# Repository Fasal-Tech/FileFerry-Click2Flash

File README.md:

# 🚀 FileFerry-Click2Flash

A compact and portable tool designed for easy factory programming of your IoT product. 🌐 Transfer files, binary images, security credentials, or certificates from an SD card or from a Serial terminal over USB to a target SPI flash IC with just a click of a button. 🎯

This repository contains all the necessary files to manufacture your own samples from JLCPCB (or a vendor of your choice) and start using it right away

The included firmware source code and compiled binaries can be used right out of the box! 🛠️ You can also modify the design and code and build your own custom product. ✨

## Product Image

The "FileFerry-Click2Flash" PCB.

The "FileFerry-Click2Flash" PCB with the pogo pins.

## 📁 Repository Contents

* **/Hardware 🛠️**
  * All Eagle design files (.brd, .sch)
* **/Firmware 💻**
  * Pre-compiled binaries to flash the board
  * Firmware source code (STM32Cube IDE, HAL) that you can use to modify the functionality
* **/Manufacturing 🏭**
  * All manufacturing files, including Gerber, BOM, PnP_XY, and prototype manufacturing files (Order BOM and PnP) that can be used to order directly from JLCPCB for a complete PCBA job.
* **/Assets 📸**
  * GitHub assets like images and other resources
* **/Demo 📸**
  * Demonstration resources to compile the firmware, flash it to the "FileFerry-Click2Flash" board and use it.

## 🔍 What is FileFerry-Click2Flash?

In its simplest form, FileFerry-Click2Flash is a low-cost, portable hardware jig that allows you to flash any external SPI flash IC (like the W25Q64JVSSIQ). 🛠️

You can transfer data in one of two ways:

1. Store your file/data in the onboard micro SD card. 💾
    1. Example: Production firmware images, common security tokens, certificates, etc.
2. Transfer the files from an external computer over UART using the X-modem protocol. 🔄
    1. Example: Device-specific unique keys, device-specific CA certificates, UUID tokens, etc.

You can do all of this with just a click of the onboard button! 🎯

## 🚀 Why is "FileFerry-Click2Flash" Needed? 🛠️

In today's fast-paced manufacturing environment, the need for efficient, reliable, and cost-effective tools is paramount. Traditional methods of programming SPI flash ICs, such as using J-link SPI programmers or bed-of-nails jigs, often involve expensive, bulky, and complex setups that are not easily adaptable to different production scenarios. 😓

This is where FileFerry-Click2Flash comes in! 🎉 It addresses the gap between high-cost, inflexible tools and the need for a versatile, portable, and user-friendly solution. Whether you are flashing firmware or transferring security credentials, or unique device identifiers, FileFerry-Click2Flash offers an ultra-low-cost alternative that is not only easy to use but also highly customizable. The ability to transfer files via an onboard SD card or over UART using the X-modem protocol provides flexibility in various production environments, making it a robust and indispensable tool for manufacturers, developers, and technicians alike. ⚙️💻

With its customizable connector interface and portable design, this tool simplifies the flashing process, reducing both the time and costs associated with traditional methods. FileFerry-Click2Flash is the modern solution to the challenges faced in programming SPI flash ICs, ensuring that the process is as seamless and efficient as possible. 🖊️💡

## 💰 Manufacturing Cost Breakdown

We got 5 quantity PCBA samples from JLCPCB. (We are in no way affiliated with JLCPCB—it's just convenient to manufacture quick prototypes with them!) 🚀

* Total cost with Shipping (PCB + PCBA): $132.49 📦
* Landing cost with import duties, customs, etc.: INR 14,000.00 (for 5 pieces) 💸
* Cost per board: INR 2,800.00 (includes 6 extra pogo pins, hand soldered later) 🛠️
* At a cost of INR 2,800.00 (~ USD 33.00), we have a SPI flasher with additional functionalities like UART transfer.
  
🔄 Compare this with a J-Flash SPI programmer at ~ USD 330.00 or a Bed of nails test jig at ~ USD 500.00.
🤔 Which would you choose?

## High Level Working

Let's look at how this works.

The "FileFerry-Click2Flash" system block diagram.

The "FileFerry-Click2Flash" PCB points

### There are two ways (currently supported) to transfer files to the target SPI Flash

### 1. Using the onboard micro SD card (Files need to be on the SD card)

  1. Simple copy the file you want to transfer to the external SPI Flash into the SD card (Example a production binary)
  2. Modify the given source code to use the file name and build the code
  3. Flash the code to the "FileFerry-Click2Flash" board
  4. Insert the SD Card, power up the board and click the "Flash" button for the flashing to take place
  5. you can monitor the progress on the RGB LED as well as debug logs on the USB-UART

### 2. Using a PC client over USB (you will need a Software client to initiate transfer)

  1. No re-programming needed.
  2. Slide the "Mode Switch" S302 to "Mode 1". This will activate UART X-Modem transfer. (Current firmware supports X-modem. Can be modified to any thing else).
  3. Open a terminal program of your choice. The terminal program has to support "File Transfer" functionality.
  4. We use TeraTerm. So open TeraTerm.
  5. Connect to the proper COM port. Use BAud as 115200,8N1.
  
  Teraterm Open

  6. Go to File-> Transfer -> XMODEM -> Send -> [Check Option 1K] + Select file.
  
  Transfer setting

  7. Select your file and click "Open".
  
  File Selection

  8. The file transfer will start.
  
  File Transfer

## What type of Files can I transfer?
The sky is the limit really. Some common examples are:

1. Transferring the production "Golden Image" of the product where the end product's bootloader performs a DFU from the binaries available in the Flash IC. (You can extend this for implementing OTA).
2. Transferring unique device CA certificates from a PC based on the device serial number. (Scan barcode, generate unique CA certificate in the PC application, transfer it to the device over USB UART).
3. Transferring audio files, JSON configuration files, etc.

## Can I modify the hardware?

You have the design files with you. You can do anything! If you are a student or a DIY'er, here are some ideas to use the hardware:

1. Use as a STM32F103 development kit
2. Use it as a data-logger. Examples:
   * Connect an I2C sensor (there is a QWIIC port for easy connection. There is also a JST port with controlled power) and modify the STM32 code to read from the sensor and store it in the onboard SD card.
   * You can connect a SPI sensor as well.
3. Use the additional UART2 port to connect a GPS receiver and modify the STM32 code to receive the GPS NMEA strings, parse it and store it in the onboard SD card.
4. RFID access control anyone? Interface a RFID reader over UART/I2C/SPI (RC522 or PN532 or similar), have a master list of RFID numbers stored in the SD card. Connect a relay to a free GPIO and give access control to the room.

Limitless possibilities!

## 📜 License Information
The hardware and firmware are released under the MIT License. 📝 The code is beerware; if you see me (or any other Fasal employee) at the local, and you've found our code helpful, please buy us a round! 🍻

Distributed as-is; no warranty is given. ⚠️ Read the License file for complete licensing information.

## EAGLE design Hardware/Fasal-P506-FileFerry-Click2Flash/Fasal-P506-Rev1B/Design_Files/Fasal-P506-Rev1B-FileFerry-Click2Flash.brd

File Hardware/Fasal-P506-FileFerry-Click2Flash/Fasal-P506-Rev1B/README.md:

# FileFerry-Click2Flash - Hardware Files #

This directory contains all the Hardware related files for the main "FileFerry-Click2Flash" Board.

# Repository Contents #
* **/Design_Files**
	* CubeMX Files
	* Change log
	* Design Report
	* Schematic pdf
	* Schematic Source (.sch)
	* Board Source (.brd)
* **/Manufacturing_Files**
	* PCBA BOM (Production Bill of Materials)
	* PCB Assembly Instructions
	* PCB Fabrication Instructions with stackup
	* Gerber Files (.zip)
	* PCB Images and 3D STEP file
	* Pick and Place (PnP_XY) files
* **/Proto_Manufacturing**
	* Use this to get a complete PCBA build from JLCPCB.
	* Gerber Files (same as production gerber)
	* JLCPCB SMT BOM (BOM for LCSC / JLCPCB PCBA)
	* JLCPCT CPL (compoennt placement file. SMD and THT both.)
* **/Testing_Files**
	* Board bring-up Arduino Test Code
	* Board Bring-up test case and report

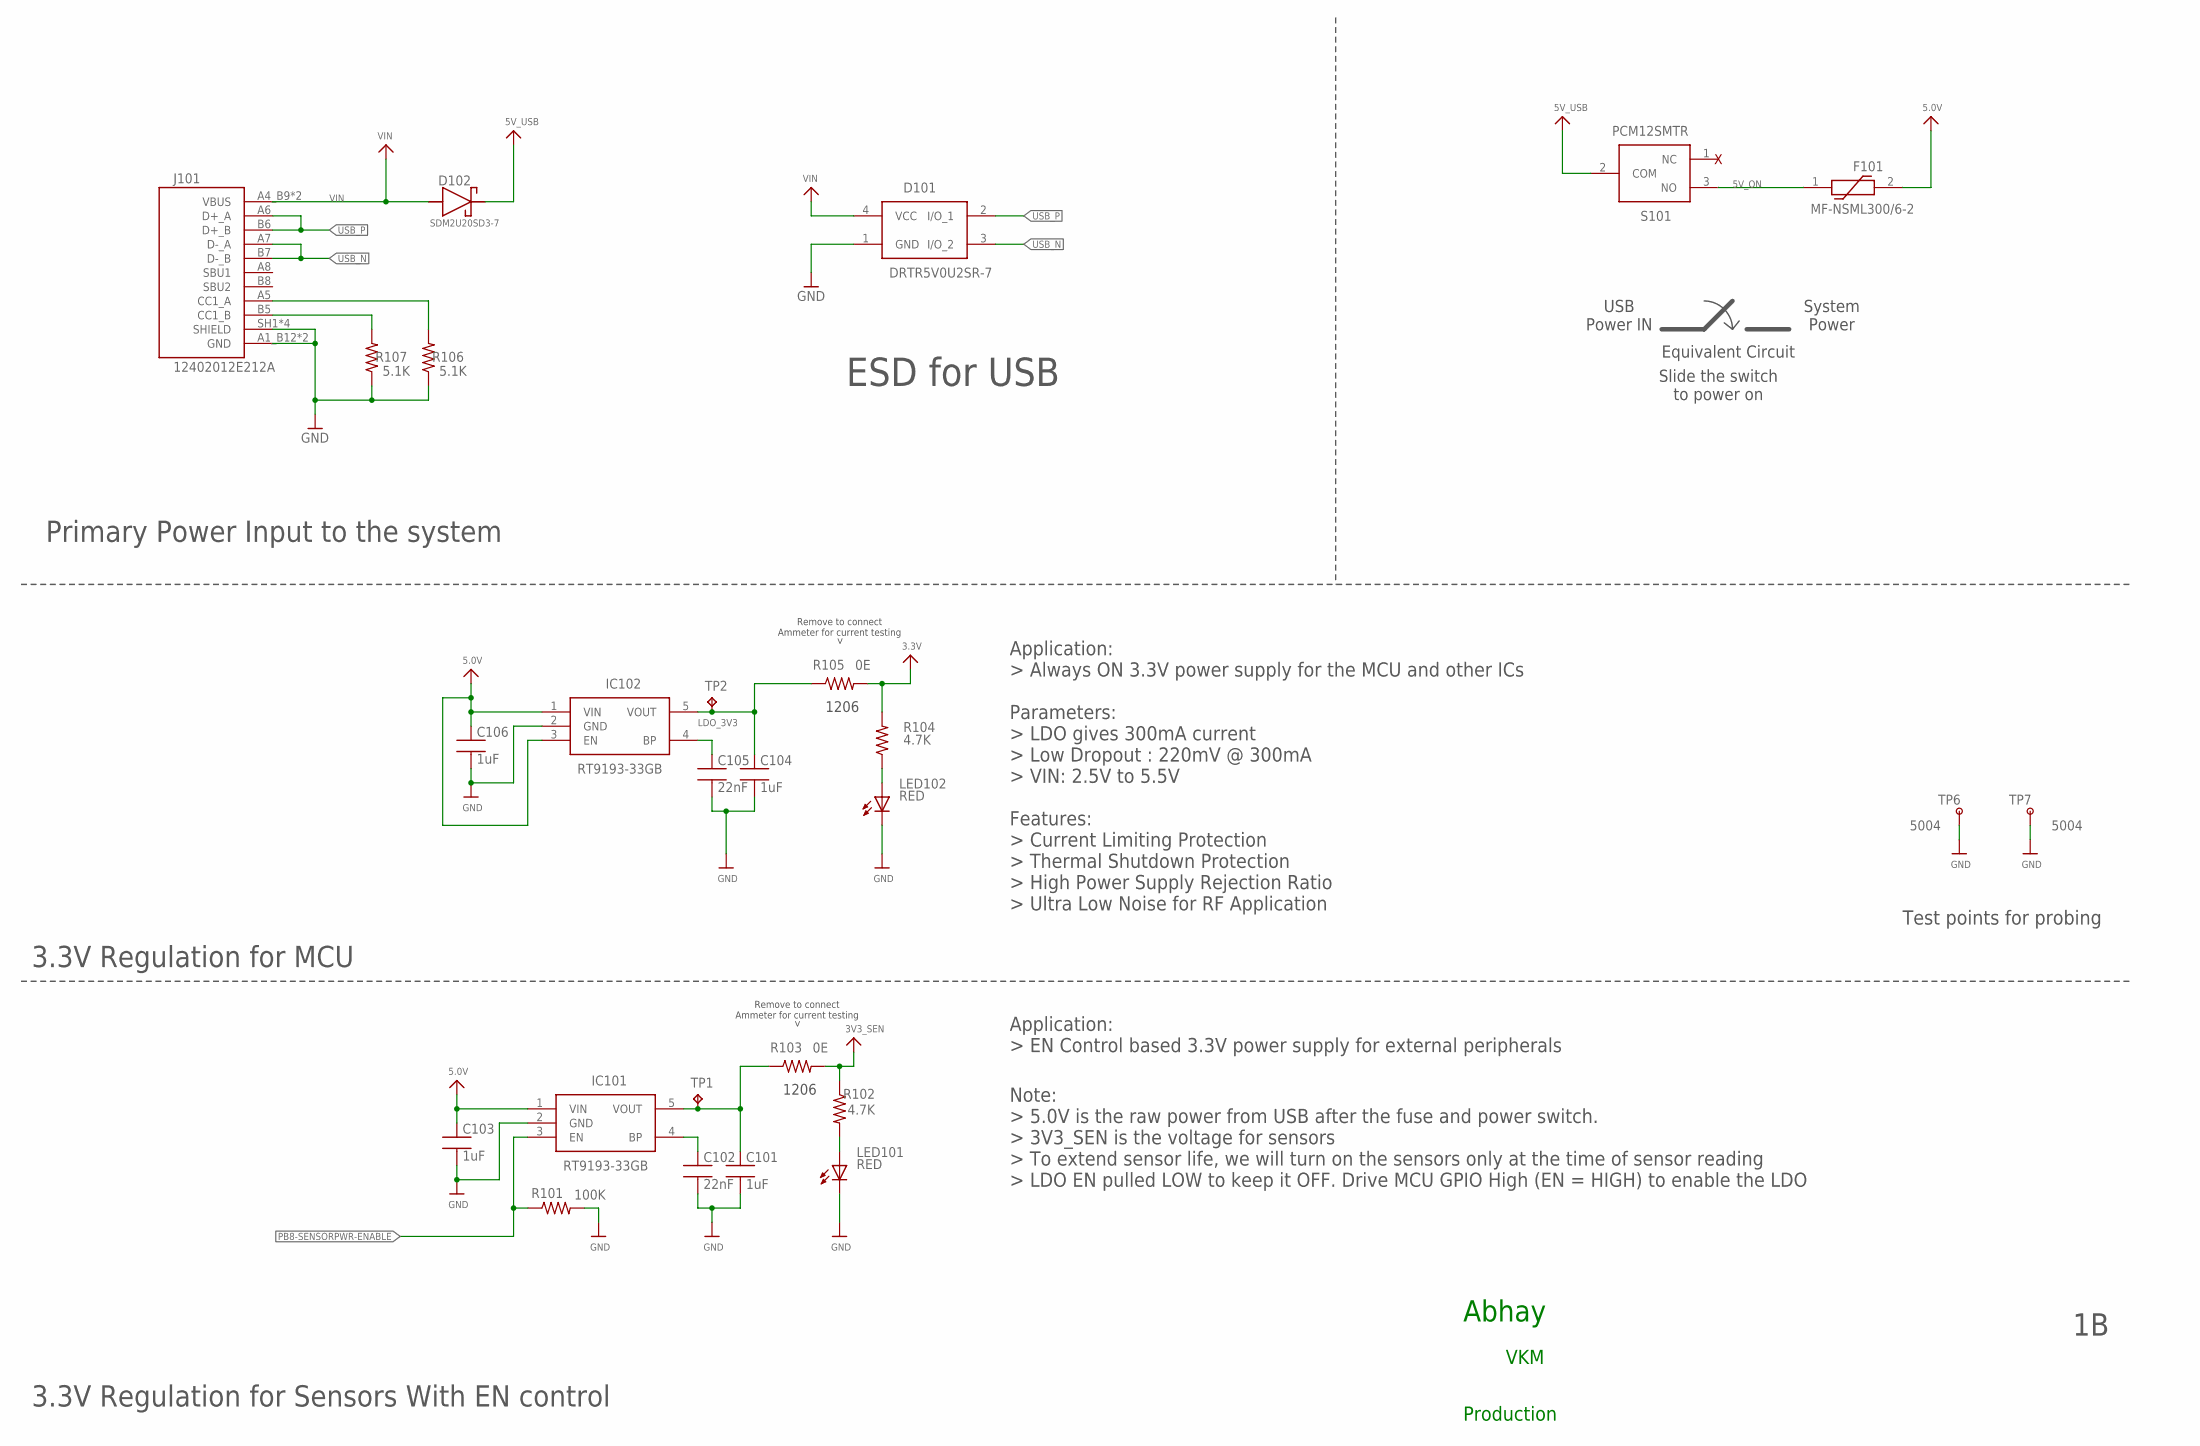
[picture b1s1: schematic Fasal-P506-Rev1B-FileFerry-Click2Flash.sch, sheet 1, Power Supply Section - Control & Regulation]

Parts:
C101, C103, C104, C106: 1uF; C0603
C102, C105: 22nF; C0603
D101: DRTR5V0U2SR-7; PRTR5V0U2X
D102: SDM2U20SD3-7; SOD2513X120N
F101: MF-NSML300/6-2; 1206L075SLYR
IC101, IC102: RT9193-33GB; SOT94P279X130-5N
J101: 12402012E212A; AMPHENOL_12402012E212A
LED101, LED102: RED; LED_CHIP_0603
R101: 100K; R0603
R102, R104: 4.7K; R0603
R103, R105: 0E; R0603
R106, R107: 5.1K; R0603
S101: PCM12SMTR
TP1, TP2: TPB1,27; B1,27
TP6, TP7: 5004

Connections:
3.3V: R104.2, R105.2; also elsewhere on the board
3V3_SEN: R102.1, R103.2; also elsewhere on the board
5.0V: C103.1, C106.1, F101.2, IC101.1 (VIN), IC102.1 (VIN), IC102.3 (EN); also elsewhere on the board
5V_ON: F101.1, S101.3 (NO)
5V_USB: D102.K, S101.2 (COM)
CC1: J101.A5 (CC1_A), R106.2
CC2: J101.B5 (CC1_B), R107.2
GND: C101.2, C102.2, C103.2, C104.2, C105.2, C106.2, D101.1 (GND), IC101.2 (GND), IC102.2 (GND), J101.A1_B12 (GND), J101.B1_A12 (GND), J101.SH1 (SHIELD), J101.SH2 (SHIELD), J101.SH3 (SHIELD), J101.SH4 (SHIELD), LED101.C, LED102.C, R101.2, R106.1, R107.1, TP6.1, TP7.1; also elsewhere on the board
LDO_3V3: C104.1, IC102.5 (VOUT), R105.1, TP2.TP
unnamed: LED102.A, R104.1
unnamed: C105.1, IC102.4 (BP)
unnamed: C101.1, IC101.5 (VOUT), R103.1, TP1.TP
unnamed: C102.1, IC101.4 (BP)
unnamed: LED101.A, R102.2
PB8-SENSORPWR-ENABLE: IC101.3 (EN), R101.1; also elsewhere on the board
USB_N: D101.3 (I/O_2), J101.A7 (D-_A), J101.B7 (D-_B); also elsewhere on the board
USB_P: D101.2 (I/O_1), J101.A6 (D+_A), J101.B6 (D+_B); also elsewhere on the board
VIN: D101.4 (VCC), D102.A, J101.A4_B9 (VBUS), J101.B4_A9 (VBUS); also elsewhere on the board

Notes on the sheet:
Abhay
3.3V Regulation for MCU
Application: > Always ON 3.3V power supply for the MCU and other ICs Parameters: > LDO gives 300mA current > Low Dropout : 220mV @ 300mA > VIN: 2.5V to 5.5V Features: > Current Limiting Protection > Thermal Shutdown Protection > High Power Supply Rejection Ratio > Ultra Low Noise for RF Application
Remove to connect Ammeter for current testing
Note: > 5.0V is the raw power from USB after the fuse and power switch. > 3V3_SEN is the voltage for sensors > To extend sensor life, we will turn on the sensors only at the time of sensor reading > LDO EN pulled LOW to keep it OFF. Drive MCU GPIO High (EN = HIGH) to enable the LDO
3.3V Regulation for Sensors With EN control
Application: > EN Control based 3.3V power supply for external peripherals
ESD for USB
Primary Power Input to the system
Slide the switch to power on
Equivalent Circuit
USB Power IN
System Power
VKM
Production
Test points for probing
1206

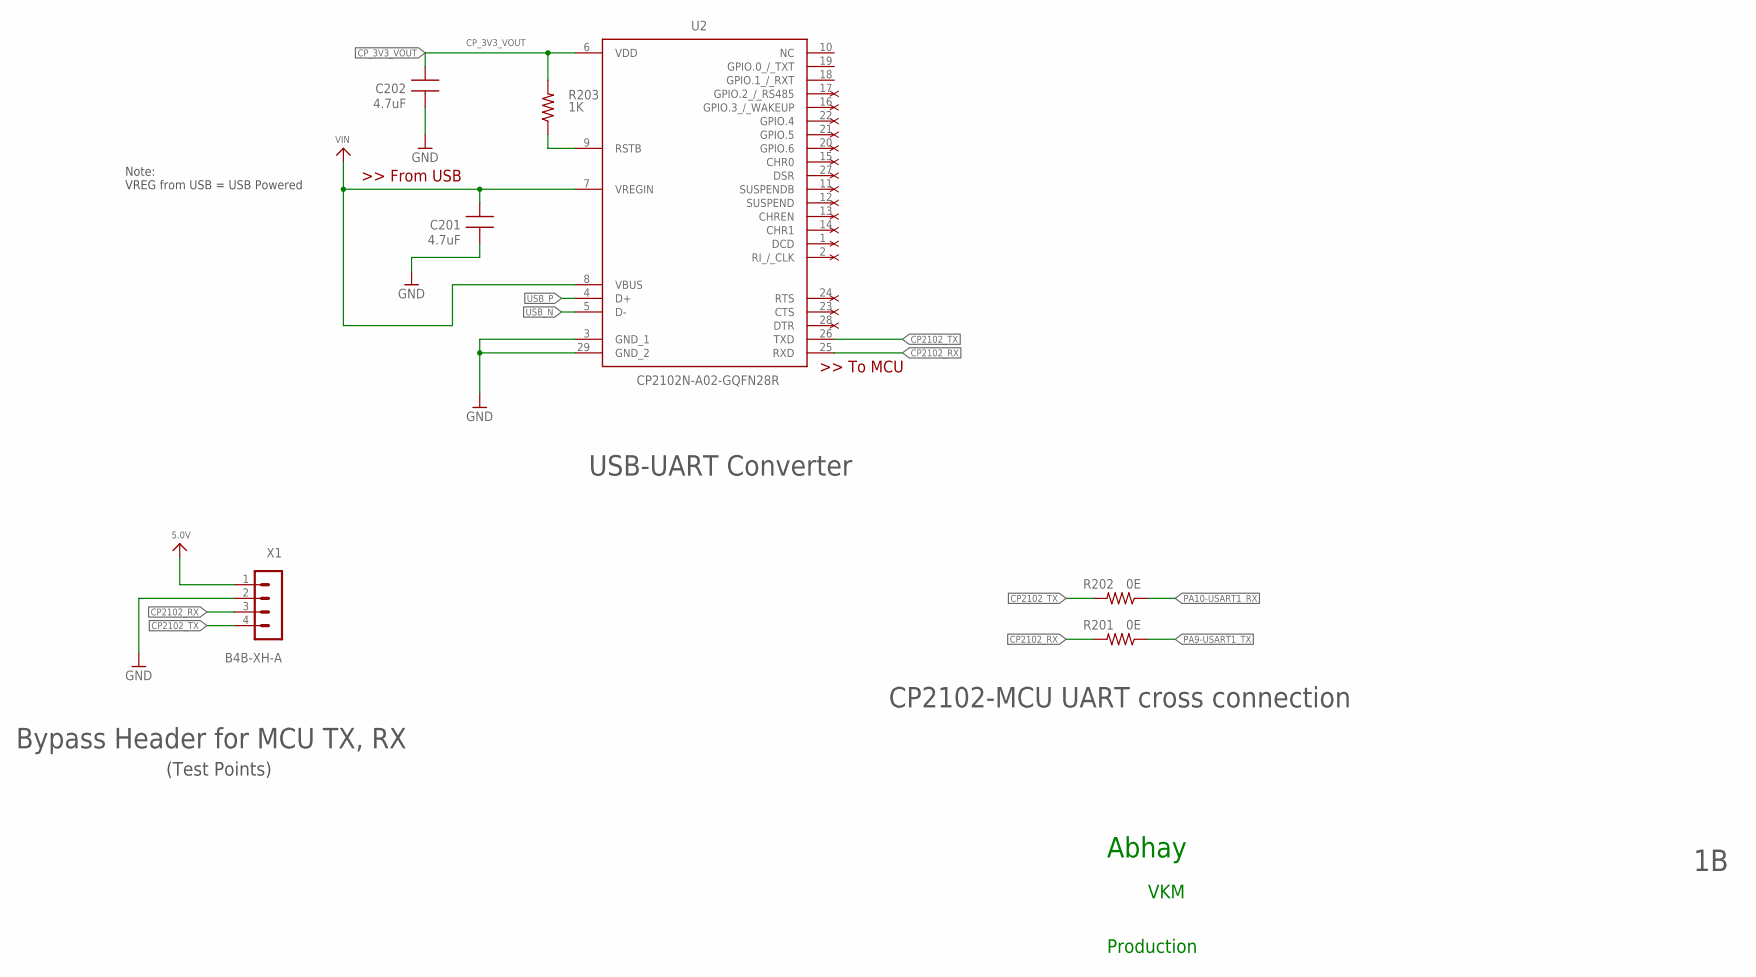
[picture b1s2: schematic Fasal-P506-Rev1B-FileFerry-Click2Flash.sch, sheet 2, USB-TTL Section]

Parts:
C201, C202: 4.7uF; C0603
R201, R202: 0E; R0603
R203: 1K; R0603
U2: CP2102N-A02-GQFN28R; QFN50P500X500X80-29N
X1: B4B-XH-A

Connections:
5.0V: X1.1; also elsewhere on the board
CP2102_RX: R201.2, U2.25 (RXD), X1.3
CP2102_TX: R202.2, U2.26 (TXD), X1.4
CP_3V3_VOUT: C202.1, R203.2, U2.6 (VDD)
GND: C201.2, C202.2, U2.3 (GND_1), U2.29 (GND_2), X1.2; also elsewhere on the board
unnamed: R203.1, U2.9 (RSTB)
PA9-USART1_TX: R201.1; also elsewhere on the board
PA10-USART1_RX: R202.1; also elsewhere on the board
USB_N: U2.5 (D-); also elsewhere on the board
USB_P: U2.4 (D+); also elsewhere on the board
VIN: C201.1, U2.7 (VREGIN), U2.8 (VBUS); also elsewhere on the board

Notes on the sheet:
Abhay
Note: VREG from USB = USB Powered
Bypass Header for MCU TX, RX
CP2102-MCU UART cross connection
USB-UART Converter
VKM
Production
(Test Points)

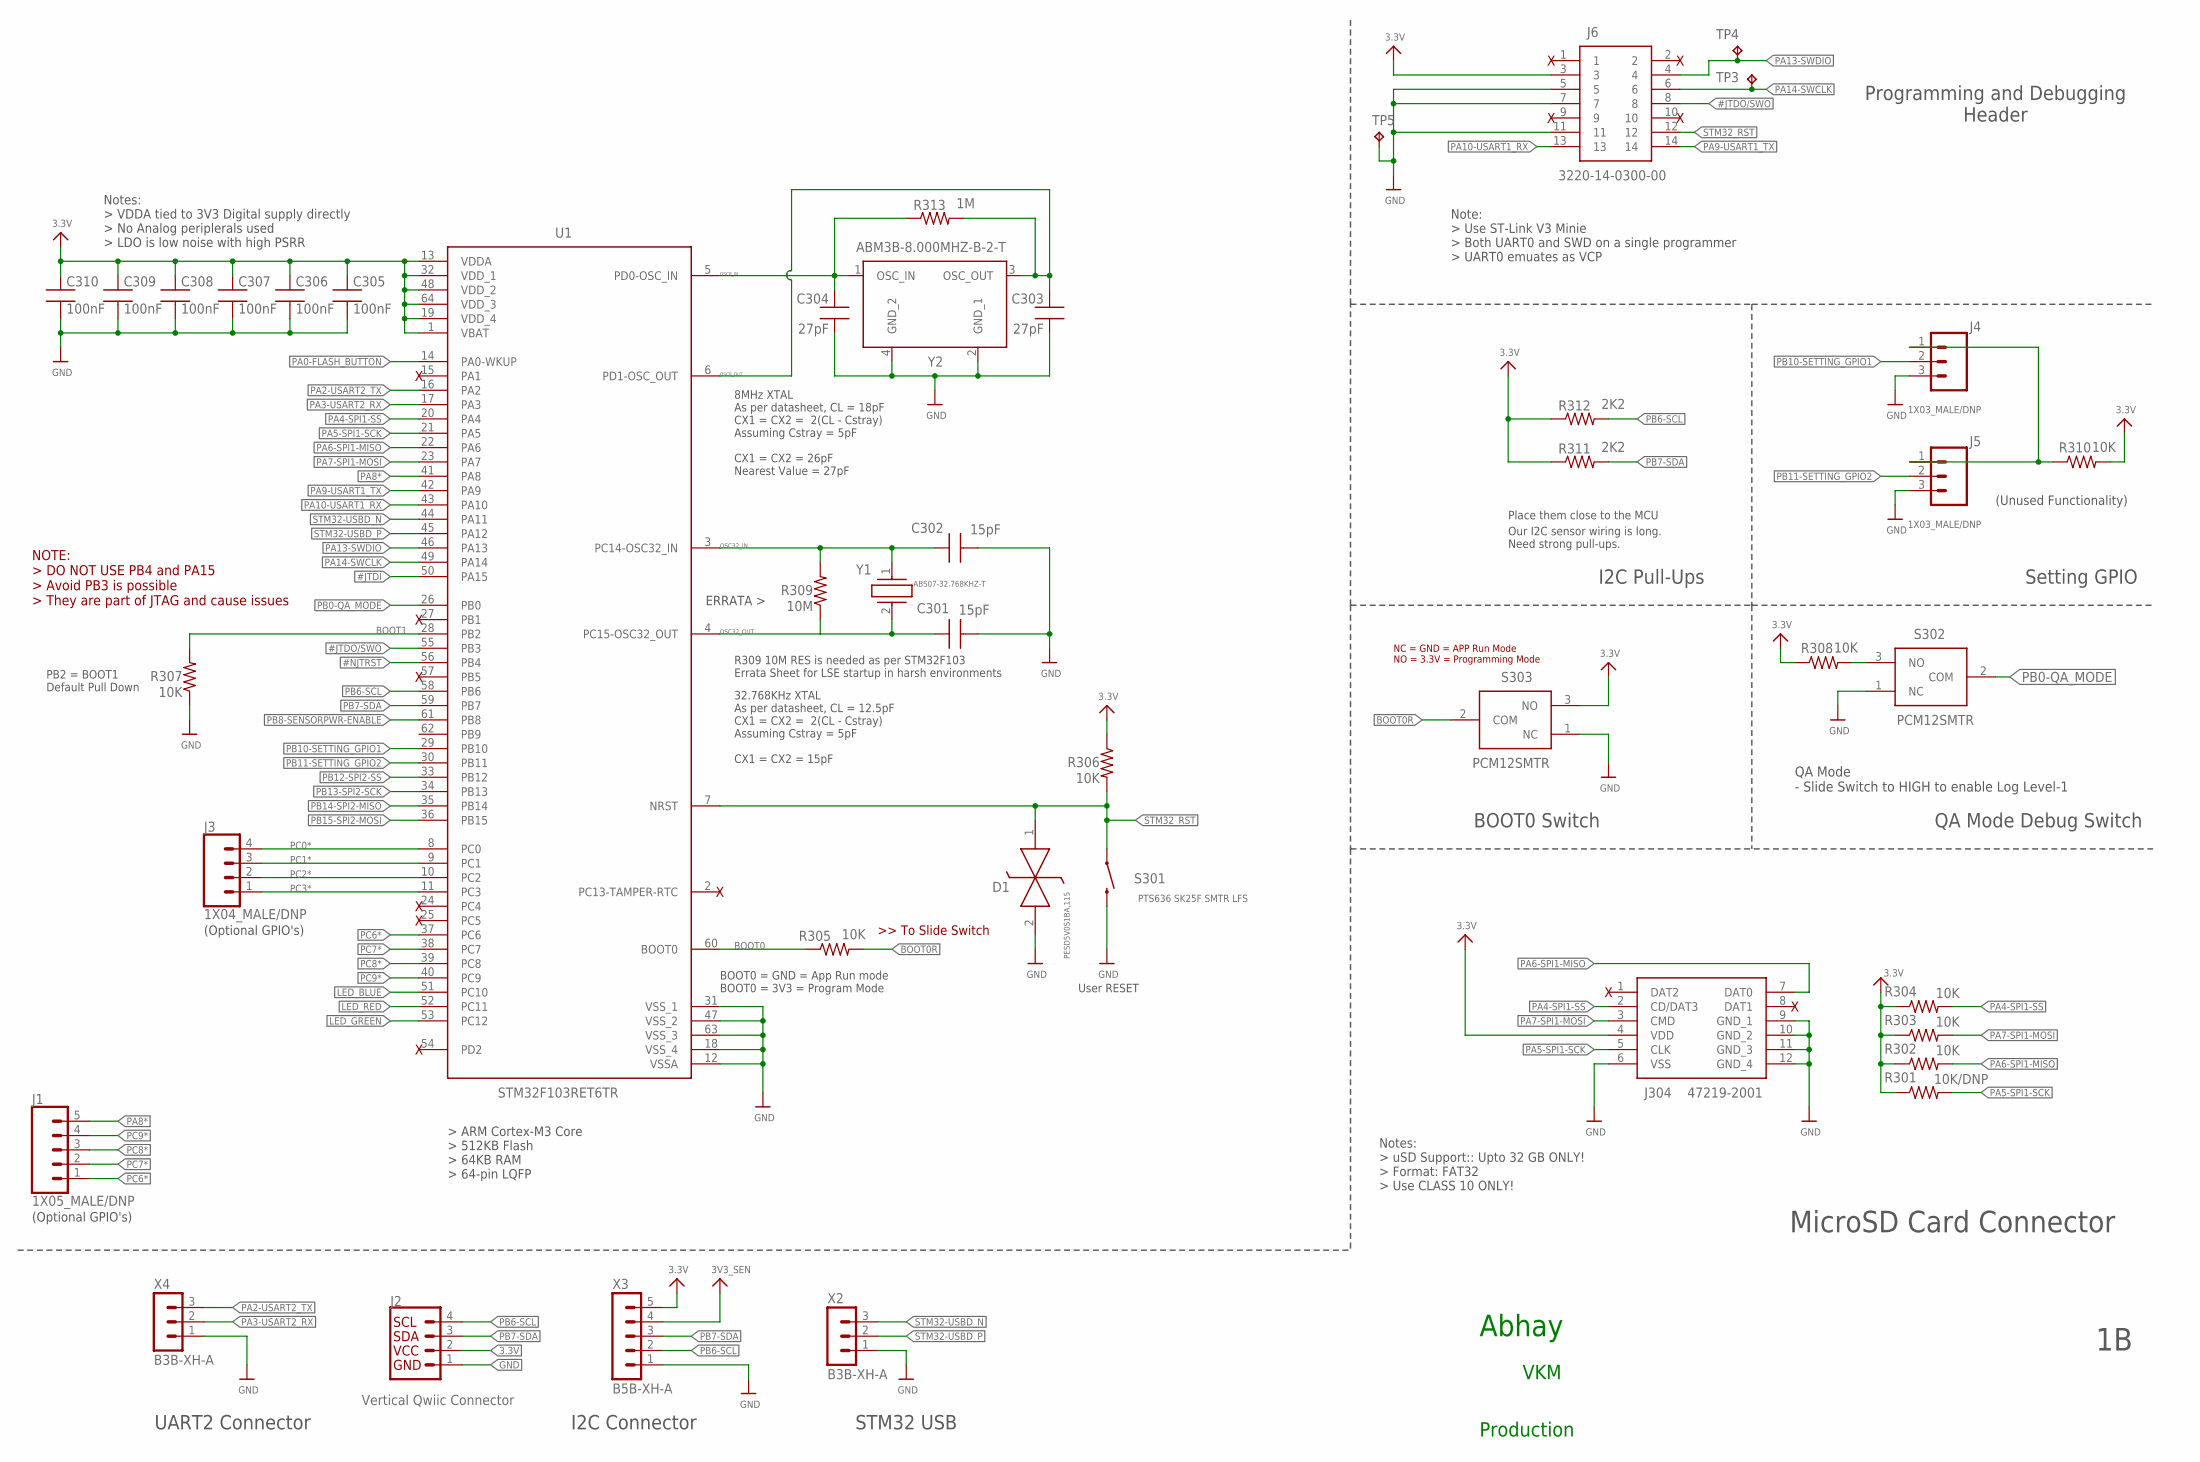
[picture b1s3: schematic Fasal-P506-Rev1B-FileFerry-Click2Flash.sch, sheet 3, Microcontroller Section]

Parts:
C301, C302: 15pF; C0603
C303, C304: 27pF; C0603
C305, C306, C307, C308, C309, C310: 100nF; C0603
D1: PESD5V0S1BA,115; SOD2512X110N
J1: 1X05_MALE/DNP; 1X05
J2: Vertical Qwiic Connector; JST04_1MM_VERT
J3: 1X04_MALE/DNP; 1X04
J4, J5: 1X03_MALE/DNP; 1X03
J6: 3220-14-0300-00; 322014030000
J304: 47219-2001; 472192001
R301: 10K/DNP; R0603
R302, R303, R304, R305, R306, R307, R308, R310: 10K; R0603
R309: 10M; R0603
R311, R312: 2K2; R0603
R313: 1M; R0603
S301: PTS636 SK25F SMTR LFS; TACTILE_SWITCH_SMD_6.0X3.5MM
S302, S303: PCM12SMTR
TP3, TP4, TP5: TPB1,27; B1,27
U1: STM32F103RET6TR; QFP50P1200X1200X160-64N
X2, X4: B3B-XH-A
X3: B5B-XH-A
Y1: ABS07-32.768KHZ-T; ABS07
Y2: ABM3B-8.000MHZ-B-2-T; ABM3B8000MHZB2T

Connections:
3.3V: C305.1, C306.1, C307.1, C308.1, C309.1, C310.1, J2.2, J6.3, J304.4 (VDD), R301.1, R302.1, R303.1, R304.1, R306.1, R308.1, R310.2, R311.1, R312.1, S303.3 (NO), U1.1 (VBAT), U1.13 (VDDA), U1.19 (VDD_4), U1.32 (VDD_1), U1.48 (VDD_2), U1.64 (VDD_3), X3.5; also elsewhere on the board
3V3_SEN: X3.4; also elsewhere on the board
#JTDI: U1.50 (PA15)
#JTDO/SWO: J6.8, U1.55 (PB3)
#NJTRST: U1.56 (PB4)
BOOT0: R305.1, U1.60 (BOOT0)
BOOT0R: R305.2, S303.2 (COM)
BOOT1: R307.2, U1.28 (PB2)
GND: C301.2, C302.2, C303.1, C304.1, C305.2, C306.2, C307.2, C308.2, C309.2, C310.2, D1.2 (K2), J2.1, J4.3, J5.3, J6.5, J6.7, J6.11, J304.6 (VSS), J304.9 (GND_1), J304.10 (GND_2), J304.11 (GND_3), J304.12 (GND_4), R307.1, S301.2, S302.1 (NC), S303.1 (NC), TP5.TP, U1.12 (VSSA), U1.18 (VSS_4), U1.31 (VSS_1), U1.47 (VSS_2), U1.63 (VSS_3), X2.1, X3.1, X4.1, Y2.2 (GND_1), Y2.4 (GND_2); also elsewhere on the board
LED_BLUE: U1.51 (PC10); also elsewhere on the board
LED_GREEN: U1.53 (PC12); also elsewhere on the board
LED_RED: U1.52 (PC11); also elsewhere on the board
unnamed: R308.2, S302.3 (NO)
unnamed: J4.1, J5.1, R310.1
OSC8_IN: C304.2, R313.1, U1.5 (PD0-OSC_IN), Y2.1 (OSC_IN)
OSC8_OUT: C303.2, R313.2, U1.6 (PD1-OSC_OUT), Y2.3 (OSC_OUT)
OSC32_IN: C302.1, R309.2, U1.3 (PC14-OSC32_IN), Y1.1
OSC32_OUT: C301.1, R309.1, U1.4 (PC15-OSC32_OUT), Y1.2
PA0-FLASH_BUTTON: U1.14 (PA0-WKUP); also elsewhere on the board
PA2-USART2_TX: U1.16 (PA2), X4.3
PA3-USART2_RX: U1.17 (PA3), X4.2
PA4-SPI1-SS: J304.2 (CD/DAT3), R304.2, U1.20 (PA4)
PA5-SPI1-SCK: J304.5 (CLK), R301.2, U1.21 (PA5)
PA6-SPI1-MISO: J304.7 (DAT0), R302.2, U1.22 (PA6)
PA7-SPI1-MOSI: J304.3 (CMD), R303.2, U1.23 (PA7)
PA8*: J1.5, U1.41 (PA8)
PA9-USART1_TX: J6.14, U1.42 (PA9); also elsewhere on the board
PA10-USART1_RX: J6.13, U1.43 (PA10); also elsewhere on the board
PA13-SWDIO: J6.4, TP4.TP, U1.46 (PA13)
PA14-SWCLK: J6.6, TP3.TP, U1.49 (PA14)
PB0-QA_MODE: S302.2 (COM), U1.26 (PB0)
PB6-SCL: J2.4, R312.2, U1.58 (PB6), X3.2
PB7-SDA: J2.3, R311.2, U1.59 (PB7), X3.3
PB8-SENSORPWR-ENABLE: U1.61 (PB8); also elsewhere on the board
PB10-SETTING_GPIO1: J4.2, U1.29 (PB10)
PB11-SETTING_GPIO2: J5.2, U1.30 (PB11)
PB12-SPI2-SS: U1.33 (PB12); also elsewhere on the board
PB13-SPI2-SCK: U1.34 (PB13); also elsewhere on the board
PB14-SPI2-MISO: U1.35 (PB14); also elsewhere on the board
PB15-SPI2-MOSI: U1.36 (PB15); also elsewhere on the board
PC0*: J3.4, U1.8 (PC0)
PC1*: J3.3, U1.9 (PC1)
PC2*: J3.2, U1.10 (PC2)
PC3*: J3.1, U1.11 (PC3)
PC6*: J1.1, U1.37 (PC6)
PC7*: J1.2, U1.38 (PC7)
PC8*: J1.3, U1.39 (PC8)
PC9*: J1.4, U1.40 (PC9)
STM32-USBD_N: U1.44 (PA11), X2.3
STM32-USBD_P: U1.45 (PA12), X2.2
STM32_RST: D1.1 (K1), J6.12, R306.2, S301.1, U1.7 (NRST)

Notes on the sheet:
Abhay
Programming and Debugging Header
QA Mode - Slide Switch to HIGH to enable Log Level-1
QA Mode Debug Switch
8MHz XTAL As per datasheet, CL = 18pF CX1 = CX2 = 2(CL - Cstray) Assuming Cstray = 5pF CX1 = CX2 = 26pF Nearest Value = 27pF
32.768KHz XTAL As per datasheet, CL = 12.5pF CX1 = CX2 = 2(CL - Cstray) Assuming Cstray = 5pF CX1 = CX2 = 15pF
R309 10M RES is needed as per STM32F103 Errata Sheet for LSE startup in harsh environments
User RESET
BOOT0 = GND = App Run mode BOOT0 = 3V3 = Program Mode
PB2 = BOOT1 Default Pull Down
I2C Pull-Ups
Place them close to the MCU
Our I2C sensor wiring is long. Need strong pull-ups.
MicroSD Card Connector
Notes: > uSD Support:: Upto 32 GB ONLY! > Format: FAT32 > Use CLASS 10 ONLY!
UART2 Connector
I2C Connector
Setting GPIO
STM32 USB
NOTE: > DO NOT USE PB4 and PA15 > Avoid PB3 is possible > They are part of JTAG and cause issues
NC = GND = APP Run Mode NO = 3.3V = Programming Mode
BOOT0 Switch
VKM
Production
ERRATA >
(Optional GPIO's)
Note: > Use ST-Link V3 Minie > Both UART0 and SWD on a single programmer > UART0 emuates as VCP
(Unused Functionality)
Notes: > VDDA tied to 3V3 Digital supply directly > No Analog periplerals used > LDO is low noise with high PSRR

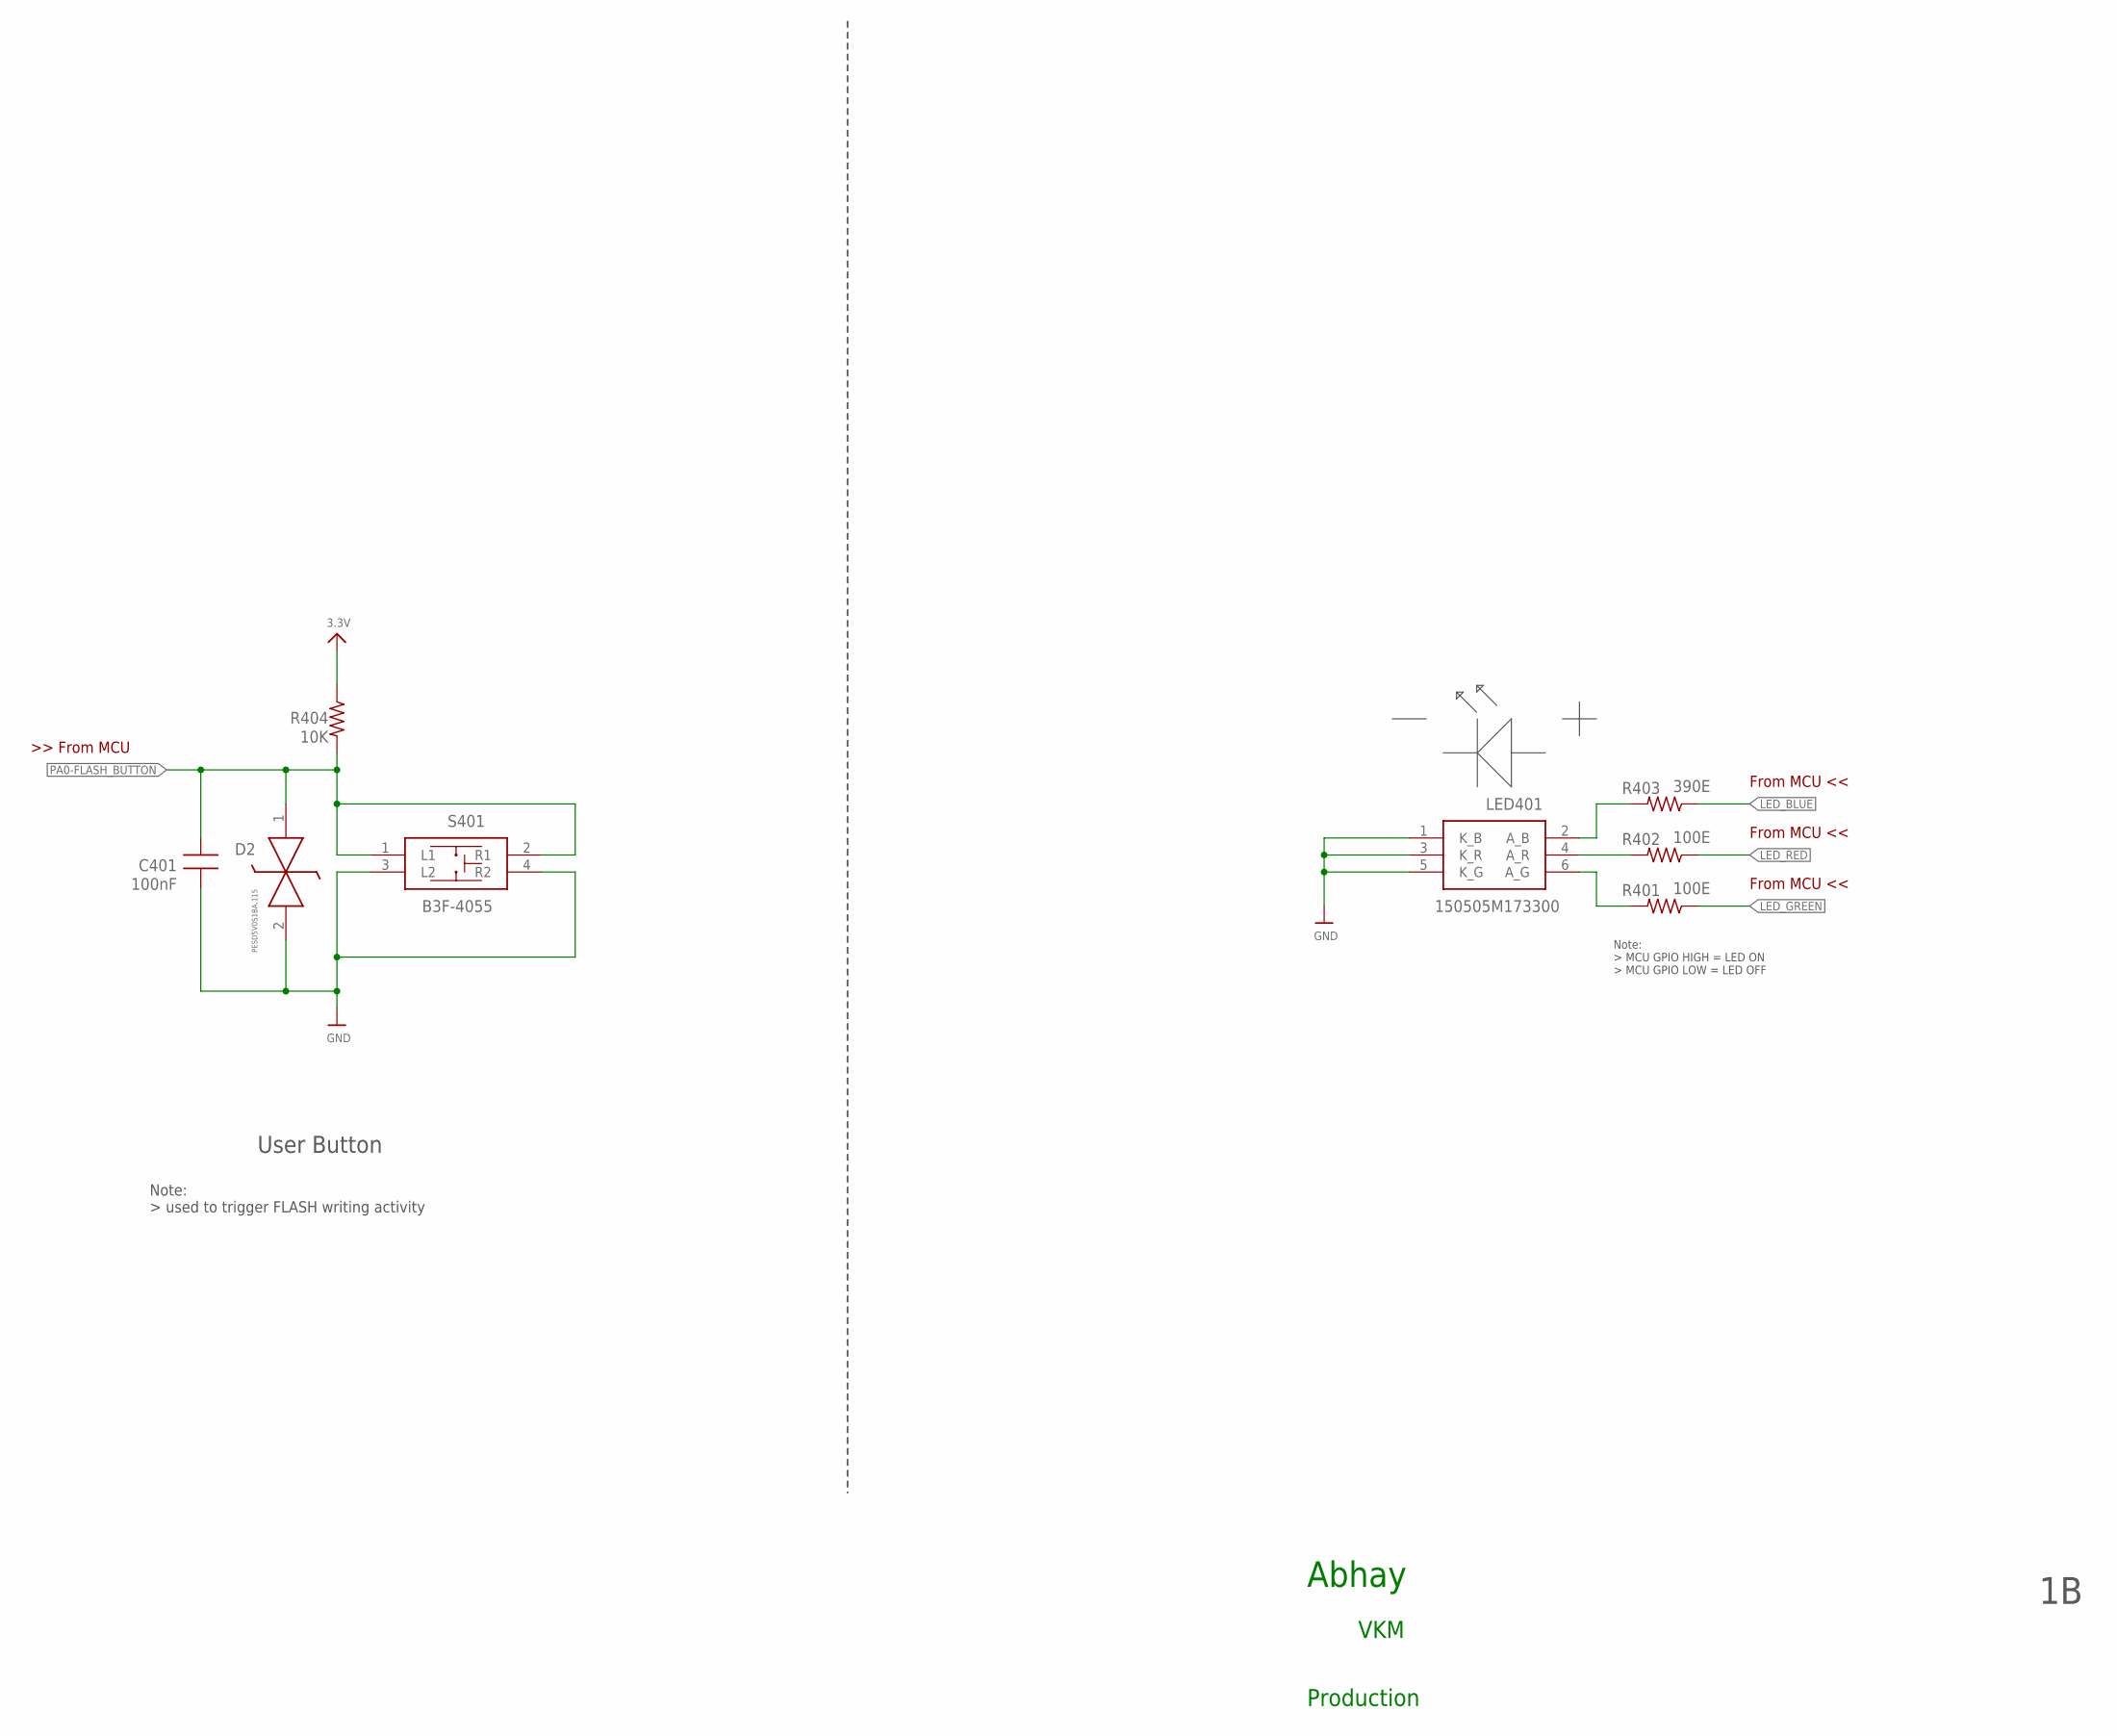
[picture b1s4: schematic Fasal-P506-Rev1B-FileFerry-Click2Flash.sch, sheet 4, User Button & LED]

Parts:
C401: 100nF; C0603
D2: PESD5V0S1BA,115; SOD2512X110N
LED401: 150505M173300
R401, R402: 100E; R0603
R403: 390E; R0603
R404: 10K; R0603
S401: B3F-4055

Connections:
3.3V: R404.1; also elsewhere on the board
GND: C401.2, D2.2 (K2), LED401.1 (K_B), LED401.3 (K_R), LED401.5 (K_G), S401.3 (L2), S401.4 (R2); also elsewhere on the board
LED_BLUE: R403.1; also elsewhere on the board
LED_GREEN: R401.1; also elsewhere on the board
LED_RED: R402.1; also elsewhere on the board
unnamed: LED401.4 (A_R), R402.2
unnamed: LED401.2 (A_B), R403.2
unnamed: LED401.6 (A_G), R401.2
PA0-FLASH_BUTTON: C401.1, D2.1 (K1), R404.2, S401.1 (L1), S401.2 (R1); also elsewhere on the board

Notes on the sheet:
Abhay
Note: > MCU GPIO HIGH = LED ON > MCU GPIO LOW = LED OFF
User Button
Note: > used to trigger FLASH writing activity
VKM
Production
From MCU <<

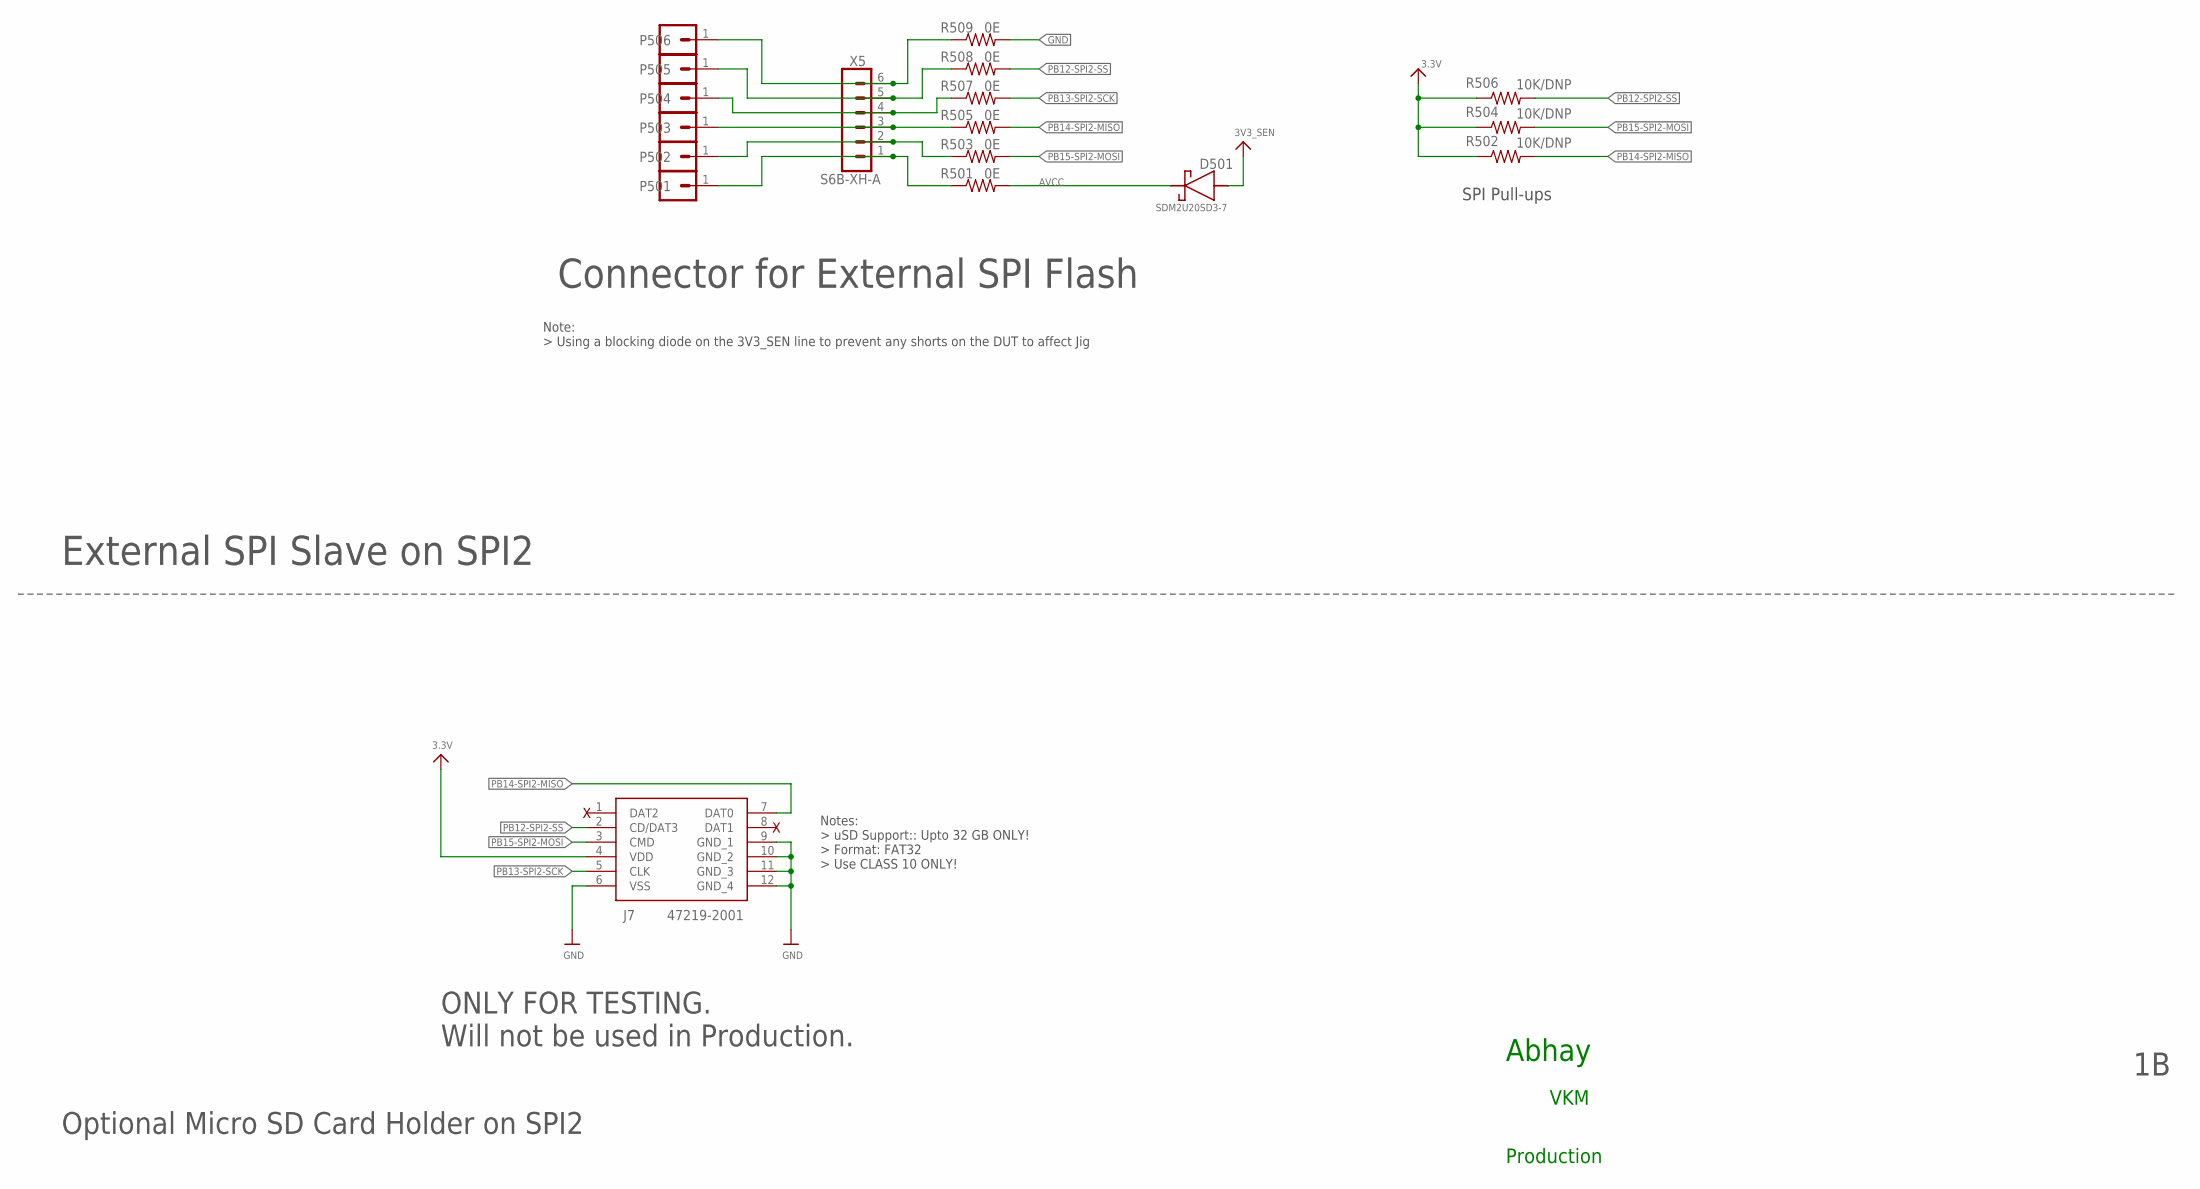
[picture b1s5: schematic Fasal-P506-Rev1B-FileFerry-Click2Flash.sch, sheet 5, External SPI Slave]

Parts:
D501: SDM2U20SD3-7; SOD2513X120N
J7: 47219-2001; 472192001
P501, P502, P503, P504, P505, P506: RA 1 pin; 1X01_SMD_PAD
R501, R503, R505, R507, R508, R509: 0E; R0603
R502, R504, R506: 10K/DNP; R0603
X5: S6B-XH-A

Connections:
3.3V: J7.4 (VDD), R502.1, R504.1, R506.1; also elsewhere on the board
3V3_SEN: D501.A; also elsewhere on the board
AVCC: D501.K, R501.2
GND: J7.6 (VSS), J7.9 (GND_1), J7.10 (GND_2), J7.11 (GND_3), J7.12 (GND_4), R509.2; also elsewhere on the board
PB12-SPI2-SS: J7.2 (CD/DAT3), R506.2, R508.2; also elsewhere on the board
PB13-SPI2-SCK: J7.5 (CLK), R507.2; also elsewhere on the board
PB14-SPI2-MISO: J7.7 (DAT0), R502.2, R505.2; also elsewhere on the board
PB15-SPI2-MOSI: J7.3 (CMD), R503.2, R504.2; also elsewhere on the board
TP-AVCC: P501.1, R501.1, X5.1
TP-GND: P506.1, R509.1, X5.6
TP-MISO: P503.1, R505.1, X5.3
TP-MOSI: P502.1, R503.1, X5.2
TP-SCK: P504.1, R507.1, X5.4
TP-SS: P505.1, R508.1, X5.5

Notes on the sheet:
Abhay
SPI Pull-ups
Connector for External SPI Flash
External SPI Slave on SPI2
Notes: > uSD Support:: Upto 32 GB ONLY! > Format: FAT32 > Use CLASS 10 ONLY!
ONLY FOR TESTING. Will not be used in Production.
Optional Micro SD Card Holder on SPI2
VKM
Production
Note: > Using a blocking diode on the 3V3_SEN line to prevent any shorts on the DUT to affect Jig

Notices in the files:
parts and their libraries:
Fasal Generic Header THT: Licensing: Creative Commons ShareAlike 4.0 International - https://creativecommons.org/licenses/by-sa/4.0
SparkFun-Aesthetics: Licensing: CC v3.0 Share-Alike You are welcome to use this library for commercial purposes.
